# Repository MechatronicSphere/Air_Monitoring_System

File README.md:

# Air_Monitoring_System
A system for monitoring the quality of air

## Collaborators
1. Masika
2. Felix Nyamongo
3. Ham Thoya 
4. Austin Masua
5. Julius Mwangi
6. Paul Mandela
7. Daniel Kariuki
8. Stephen Ngige
9. washington otieno
10. Faith Ndila
11.Vincent murimi
12.Eric Ndumia

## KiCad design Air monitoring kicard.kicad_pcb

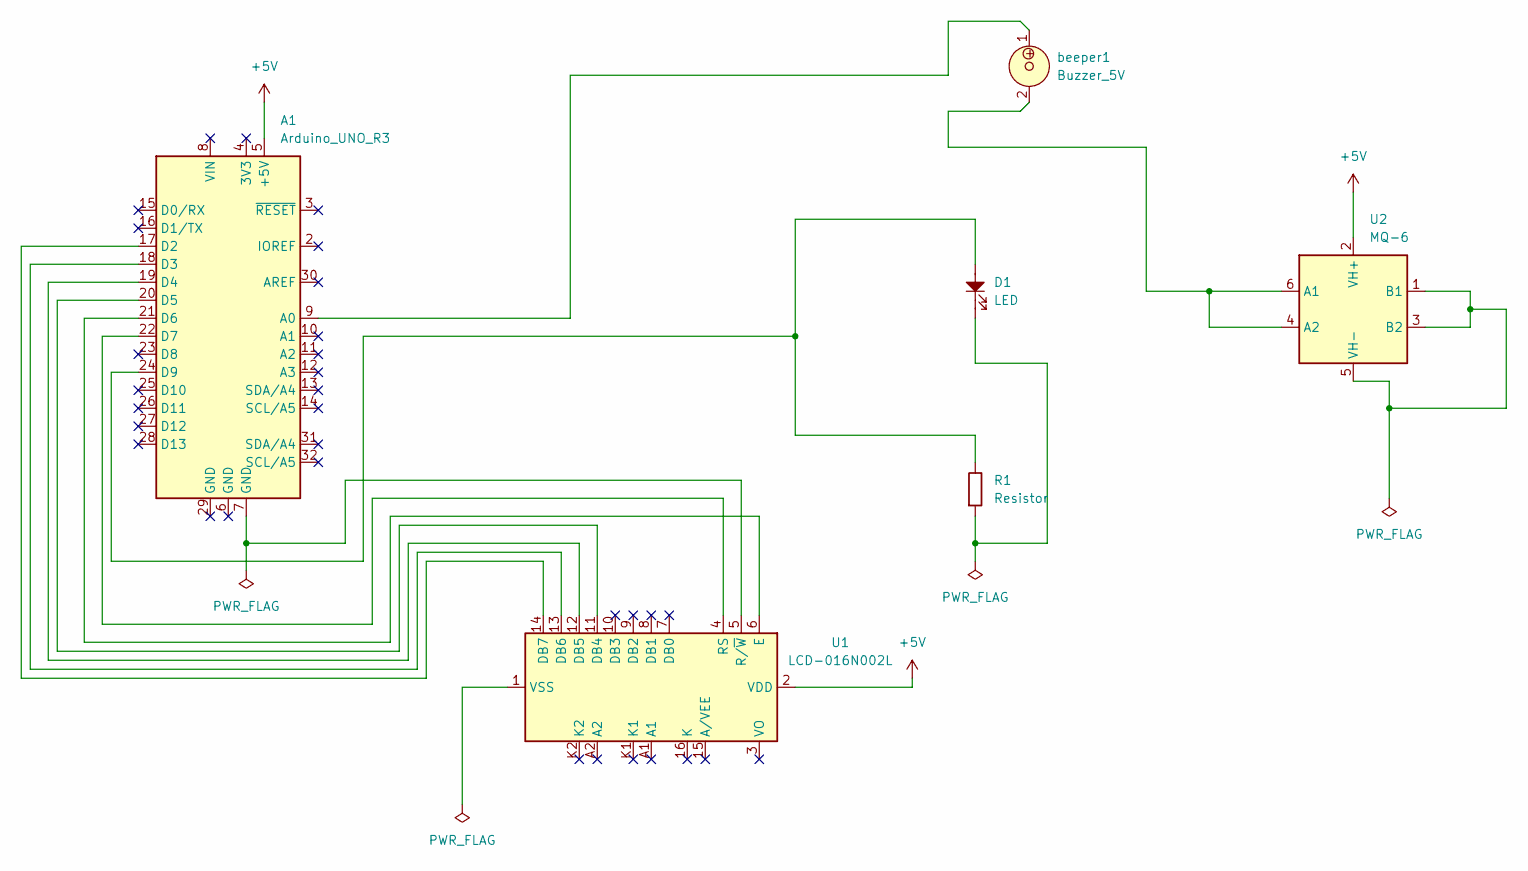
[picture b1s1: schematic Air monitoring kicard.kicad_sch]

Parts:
A1: Arduino_UNO_R3
D1: LED; LED_D5.0mm
R1: Resistor; R_Axial_DIN0207_L6.3mm_D2.5mm_P10.16mm_Horizontal
U1: LCD-016N002L
U2: MQ-6
beeper1: Buzzer_5V; MagneticBuzzer_ProSignal_ABT-410-RC

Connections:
+5V: A1.5 (+5V), U1.2 (VDD), U2.2 (VH+)
unnamed: A1.9 (A0), beeper1.1
unnamed: A1.17 (D2), U1.14 (DB7)
unnamed: A1.18 (D3), U1.13 (DB6)
unnamed: A1.19 (D4), U1.12 (DB5)
unnamed: A1.20 (D5), U1.11 (DB4)
unnamed: A1.21 (D6), U1.6 (E)
unnamed: A1.22 (D7), U1.4 (RS)
unnamed: A1.24 (D9), D1.2, R1.2
unnamed: D1.1, R1.1
unnamed: A1.7 (GND), U1.5 (R/~W)
unnamed: U2.4 (A2), U2.6 (A1), beeper1.2
unnamed: U2.1 (B1), U2.3 (B2), U2.5 (VH-)

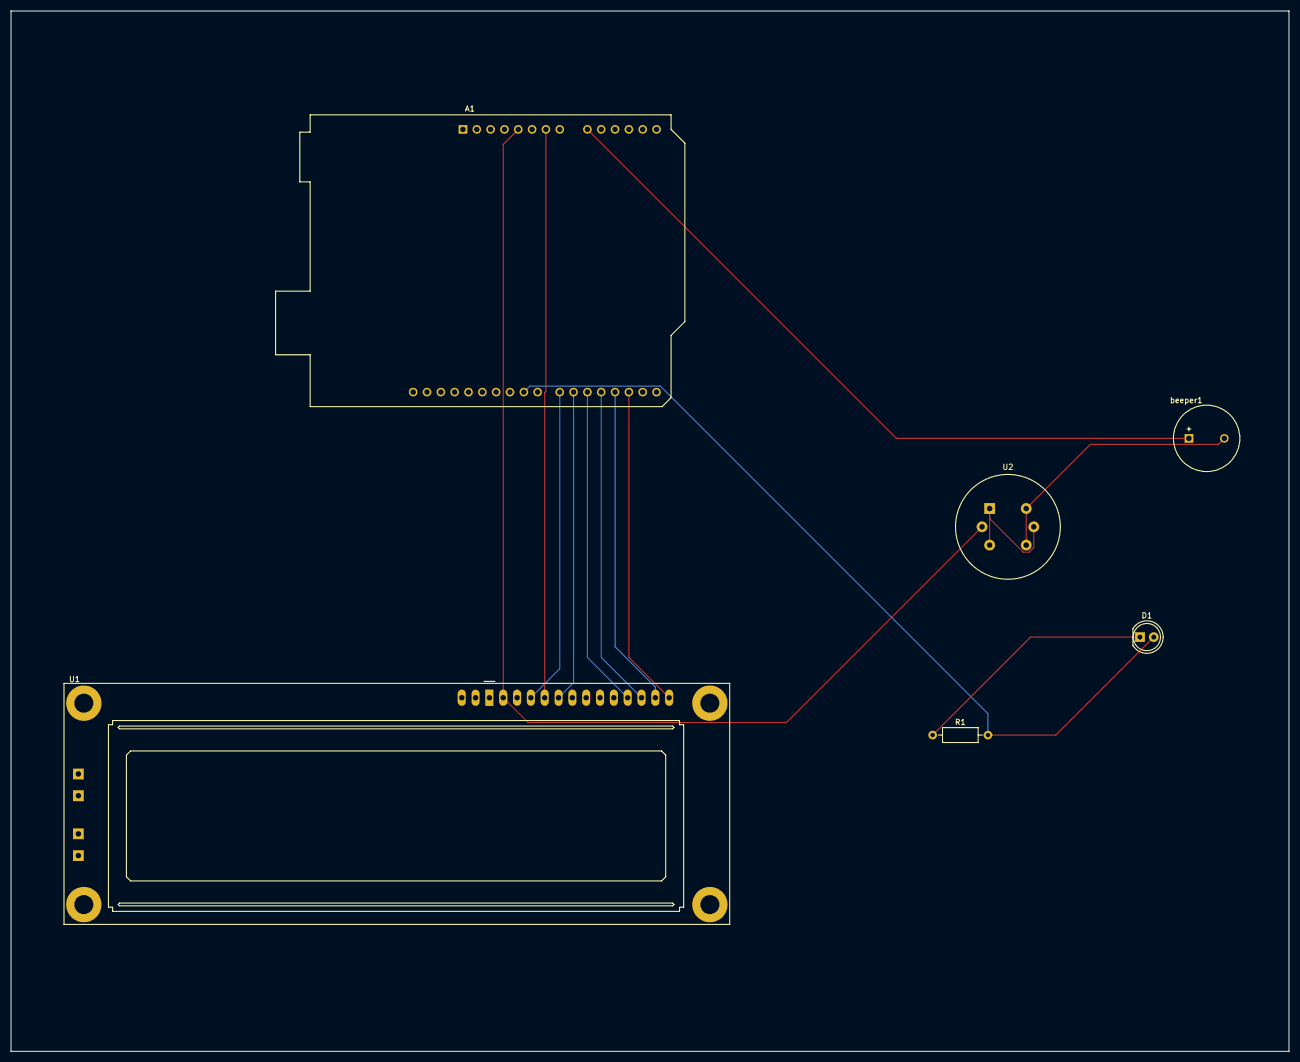
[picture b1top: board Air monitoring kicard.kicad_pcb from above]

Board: 2 copper layers, 234.8 x 191.1 mm, 6 parts (0 on the bottom side), 13 nets.

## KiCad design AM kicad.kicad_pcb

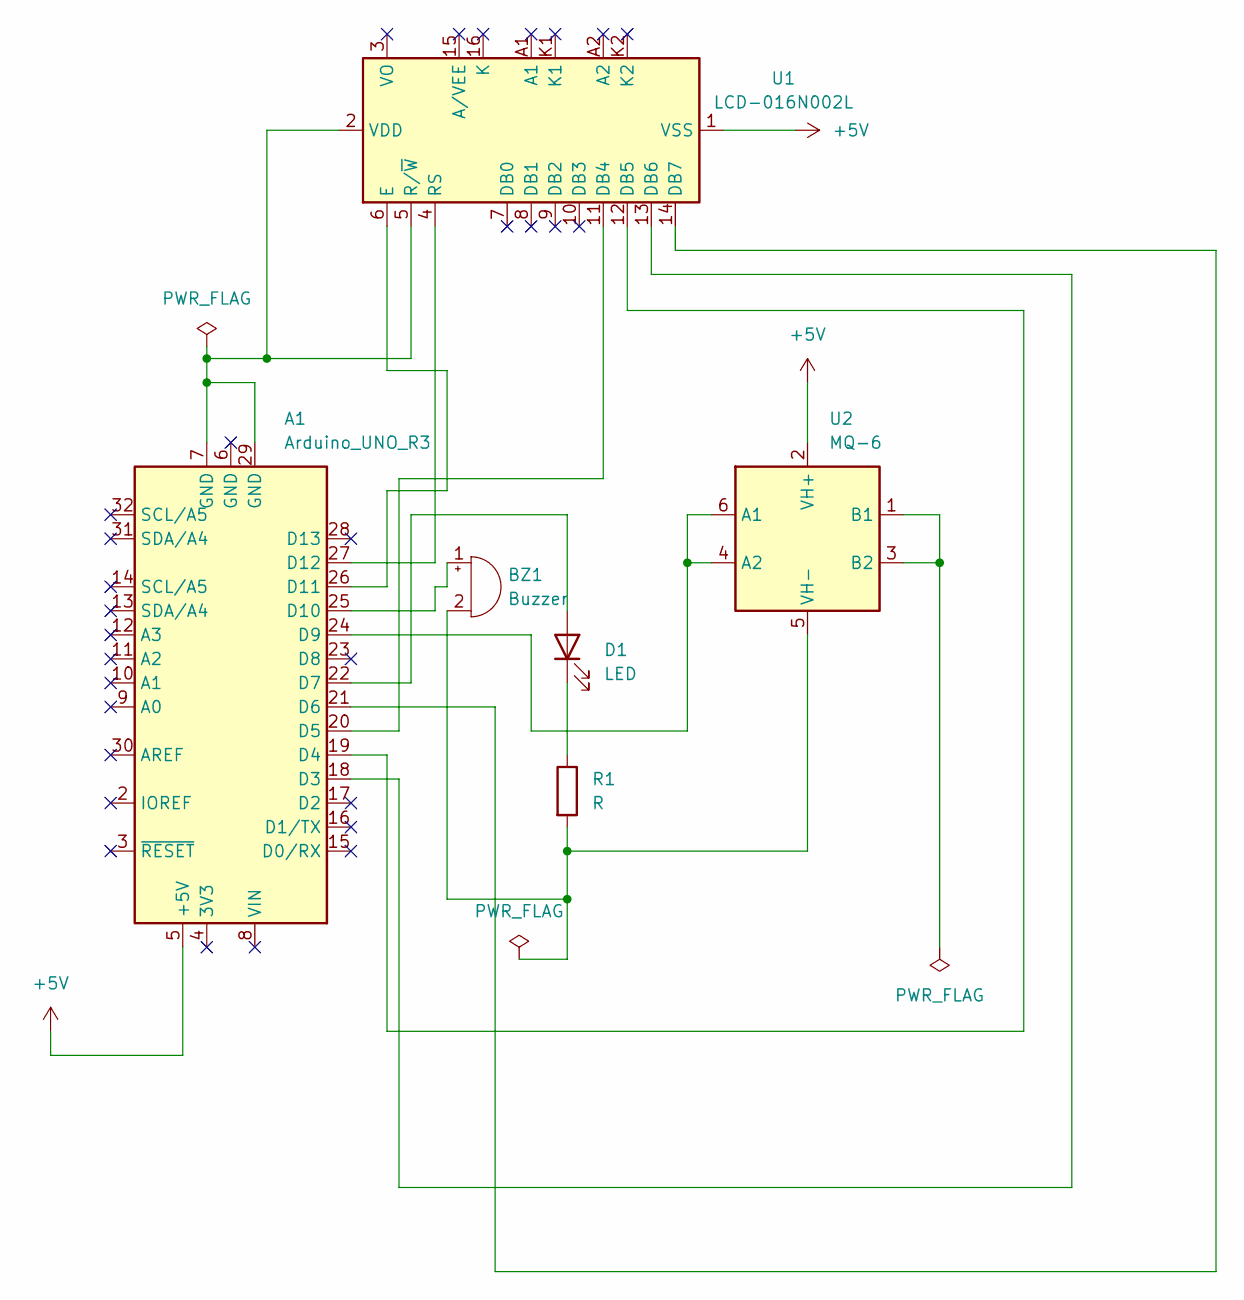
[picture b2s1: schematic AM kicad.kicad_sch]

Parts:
A1: Arduino_UNO_R3
BZ1: Buzzer; Buzzer_12x9.5RM7.6
D1: LED; LED_D3.0mm
R1: R; R_Axial_DIN0207_L6.3mm_D2.5mm_P5.08mm_Vertical
U1: LCD-016N002L
U2: MQ-6

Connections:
+5V: A1.5 (+5V), U1.1 (VSS), U2.2 (VH+)
unnamed: A1.18 (D3), U1.13 (DB6)
unnamed: A1.19 (D4), U1.12 (DB5)
unnamed: A1.20 (D5), U1.11 (DB4)
unnamed: A1.21 (D6), U1.14 (DB7)
unnamed: A1.22 (D7), D1.2 (A)
unnamed: A1.24 (D9), U2.4 (A2), U2.6 (A1)
unnamed: A1.25 (D10), BZ1.1 (+)
unnamed: A1.26 (D11), U1.6 (E)
unnamed: A1.27 (D12), U1.4 (RS)
unnamed: BZ1.2 (-), R1.2, U2.5 (VH-)
unnamed: D1.1 (K), R1.1
unnamed: A1.7 (GND), A1.29 (GND), U1.2 (VDD), U1.5 (R/~W)
unnamed: U2.1 (B1), U2.3 (B2)

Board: 2 copper layers, 6 parts (0 on the bottom side), 14 nets, no tracks yet.

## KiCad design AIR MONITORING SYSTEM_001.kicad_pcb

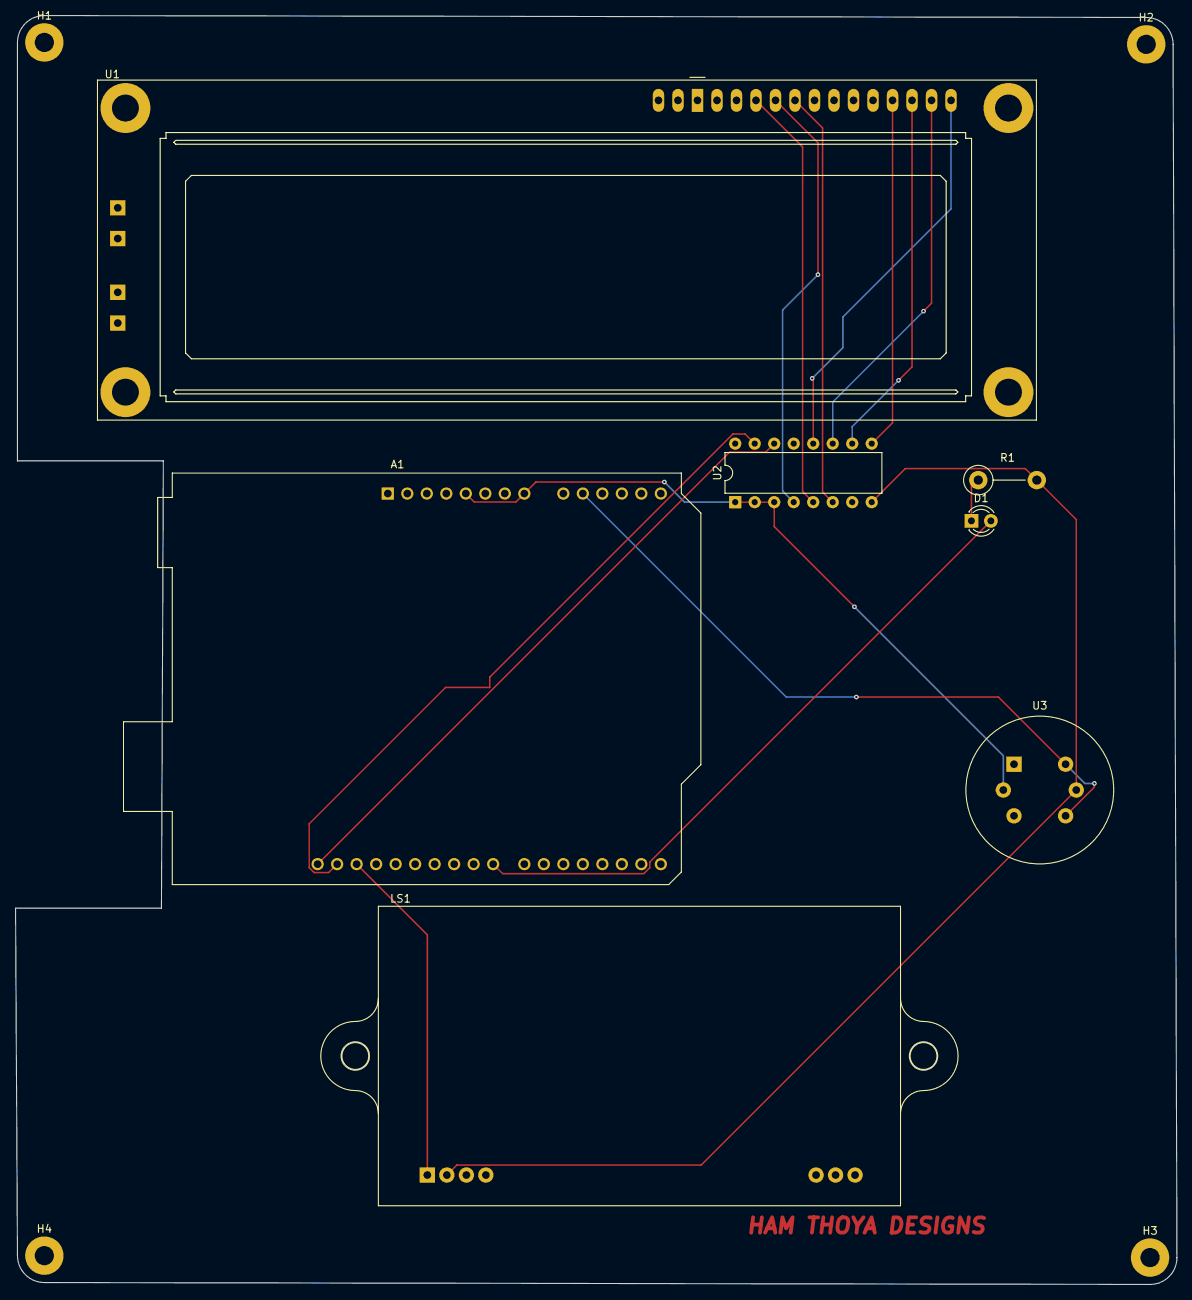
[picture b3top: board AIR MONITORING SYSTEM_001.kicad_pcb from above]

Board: 2 copper layers, 151.2 x 165.2 mm, 11 parts (0 on the bottom side), 15 nets.

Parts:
A1: Arduino_UNO_R3
D1: LED; LED_D3.0mm_Clear
H1, H2, H3, H4: MountingHole_Pad; MountingHole_2.5mm_Pad
LS1: Speaker; Reverb_BTDR-1H
R1: R_Small_US; R_Axial_DIN0411_L9.9mm_D3.6mm_P7.62mm_Vertical
U1: LCD-016N002L
U2: PCF8574P; DIP-16_W7.62mm
U3: MQ-6

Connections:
+5V: A1.5 (+5V), A1.8 (VIN), U2.1 (A0), U2.2 (A1), U2.3 (A2), U3.2 (VH+)
/BZ: A1.30 (AREF), LS1.1
/D4: U1.11 (DB4), U2.9 (P4)
/D5: U1.12 (DB5), U2.10 (P5)
/D6: U1.13 (DB6), U2.11 (P6)
/D7: U1.14 (DB7), U2.12 (P7)
/E: U1.6 (E), U2.6 (P2)
/LED: A1.23 (D8), D1.2 (A)
/OUT: A1.10 (A1), U3.4 (A2), U3.6 (A1)
/RS: U1.5 (R/~W), U2.4 (P0)
/R/W: U1.4 (RS), U2.5 (P1)
/SCL: A1.32 (SCL/A5), U2.14 (SCL)
/SDA: A1.31 (SDA/A4), U2.15 (SDA)
Earth: LS1.2, R1.2, U2.8 (GND), U3.5 (VH-)
unnamed: D1.1 (K), R1.1

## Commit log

2026-01-29 another commit
2026-02-02 Kicad designs and mechanical design
